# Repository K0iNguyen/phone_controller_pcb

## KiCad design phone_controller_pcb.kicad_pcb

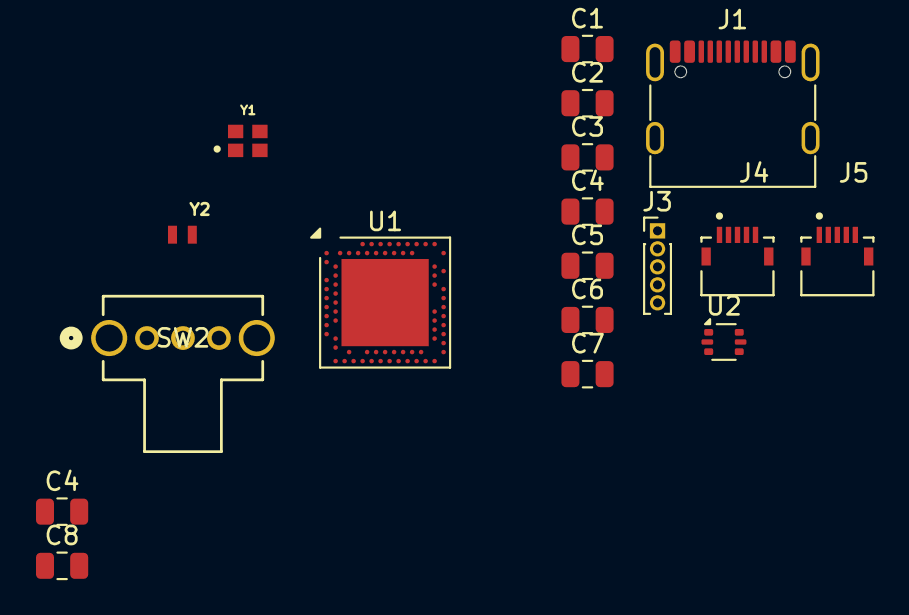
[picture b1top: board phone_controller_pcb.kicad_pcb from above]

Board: 2 copper layers, 18 parts (0 on the bottom side), 27 nets, no tracks yet.

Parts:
C1: 100nF; C_0805_2012Metric
C2, C4#2, C6: C; C_0805_2012Metric
C3: 100pF; C_0805_2012Metric
C4: 1uF; C_0805_2012Metric
C5: 820pF; C_0805_2012Metric
C7: 4.7uF; C_0805_2012Metric
C8: 47nF; C_0805_2012Metric
J1: USB_C_Receptacle_USB2.0_14P; USB_C_Receptacle_G-Switch_GT-USB-7010ASV
J3: Conn_01x05_Pin; PinHeader_1x05_P1.00mm_Vertical
J4, J5: Conn_01x05_Pin; AMPHENOL_59453-052110ECHLF
SW2: SW_SPDT_312; OS102011MA1QN1_CNK
U1: nRF52840; Nordic_AQFN-73-1EP_7x7mm_P0.5mm
U2: USBLC6-2P6; SOT-666
Y1: ECS-320-8-37B-CKY-TR; XTAL_ECS-160-9-37-CKM-TR
Y2: ABS05-32.768KHZ-9-T; XTAL_ABS05-32.768KHZ-9-T

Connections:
+3.3V: J3.5, J4.3, J5.3, U1.A22 (VDD), U1.AD14 (VDD), U1.AD23 (VDD), U1.B1 (VDD), U1.W1 (VDD), U1.Y2 (VDDH)
+5V: SW2.2 (C), U1.AD2 (VBUS)
/DEC1: C1.1, U1.C1 (DEC1)
/DEC2: C2.1, U1.A18 (DEC2)
/DEC3: C3.1, U1.D23 (DEC3)
/DEC4_6: C4.1, C8.1, U1.B5 (DEC4), U1.E24 (DEC6)
/DEC5: C5.1, U1.N24 (DEC5)
/DECUSB: C7.1, U1.AC5 (DECUSB)
/S1: J4.5, U1.G1 (P0.26)
/S2: J5.5, U1.H2 (P0.27)
/SWDCLK: J3.2, U1.AA24 (SWDCLK)
/SWDIO: J3.3, U1.AC24 (SWDIO)
/USB_D+: U1.AD6 (D+), U2.4 (I/O2)
/USB_D-: U1.AD4 (D-), U2.6 (I/O1)
/X1: J4.2, U1.B11 (AIN4/P0.28)
/X2: J5.2, U1.B9 (AIN6/P0.30)
/XC_IN: U1.B24 (XC1), Y1.1 (IN/OUT)
/XC_OUT: U1.A23 (XC2), Y1.3 (OUT/IN)
/Y1: J4.4, U1.A10 (AIN5/P0.29)
/Y2: J5.4, U1.A8 (AIN7/P0.31)
/nRESET: J3.1, U1.AC13 (P0.18/~RESET)
GND: C1.2, C2.2, C3.2, C4.2, C4#2.2, C5.2, C6.2, C7.2, C8.2, J1.A1 (GND), J1.A12 (GND), J1.B1 (GND), J1.B12 (GND), J3.4, J4.1, J5.1, U1.B7 (VSS), U1.EP (VSS), U1.F23 (VSS_PA), U2.2 (GND), Y1.2 (GND), Y1.4 (GND__1)
unnamed: J1.A6 (D+), J1.B6 (D+), U2.3 (I/O2)
unnamed: J1.A7 (D-), J1.B7 (D-), U2.1 (I/O1)
unnamed: U1.D2 (XL1/P0.00), Y2.1
unnamed: U1.F2 (XL2/P0.01), Y2.2
VBUS: J1.A4 (VBUS), J1.A9 (VBUS), J1.B4 (VBUS), J1.B9 (VBUS), SW2.1 (B), U2.5 (VBUS)
